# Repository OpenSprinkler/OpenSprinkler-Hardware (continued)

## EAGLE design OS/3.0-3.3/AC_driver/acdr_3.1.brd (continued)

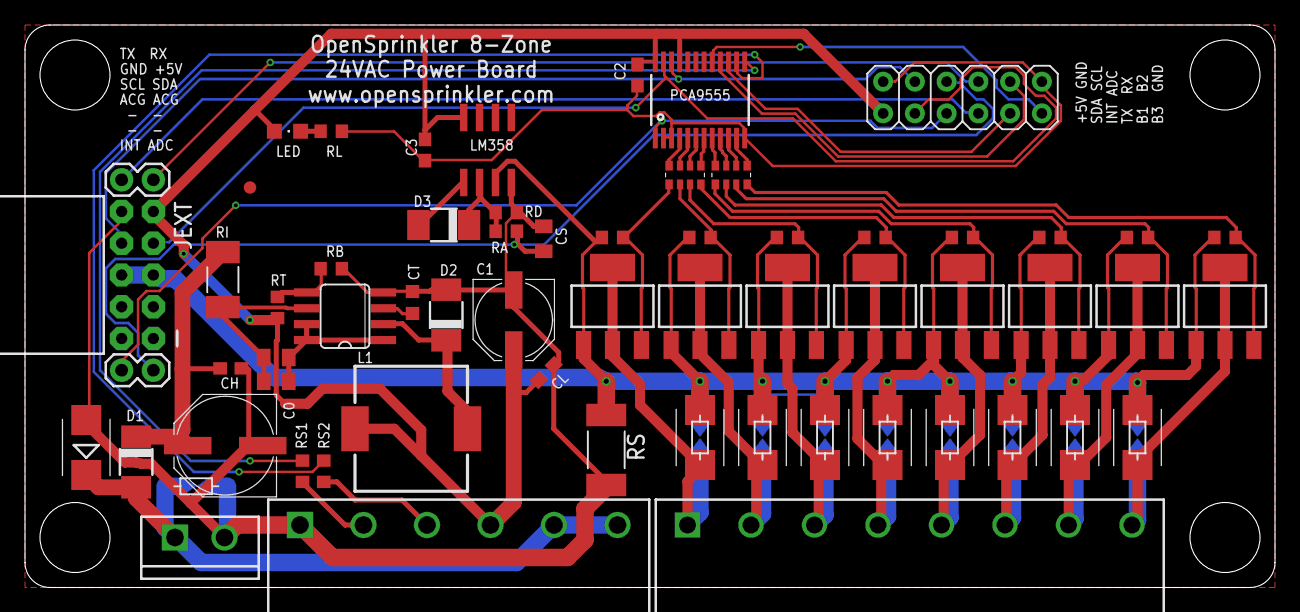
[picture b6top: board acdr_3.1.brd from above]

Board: 2 copper layers, 100.0 x 45.0 mm, 71 parts (0 on the bottom side), 50 nets.

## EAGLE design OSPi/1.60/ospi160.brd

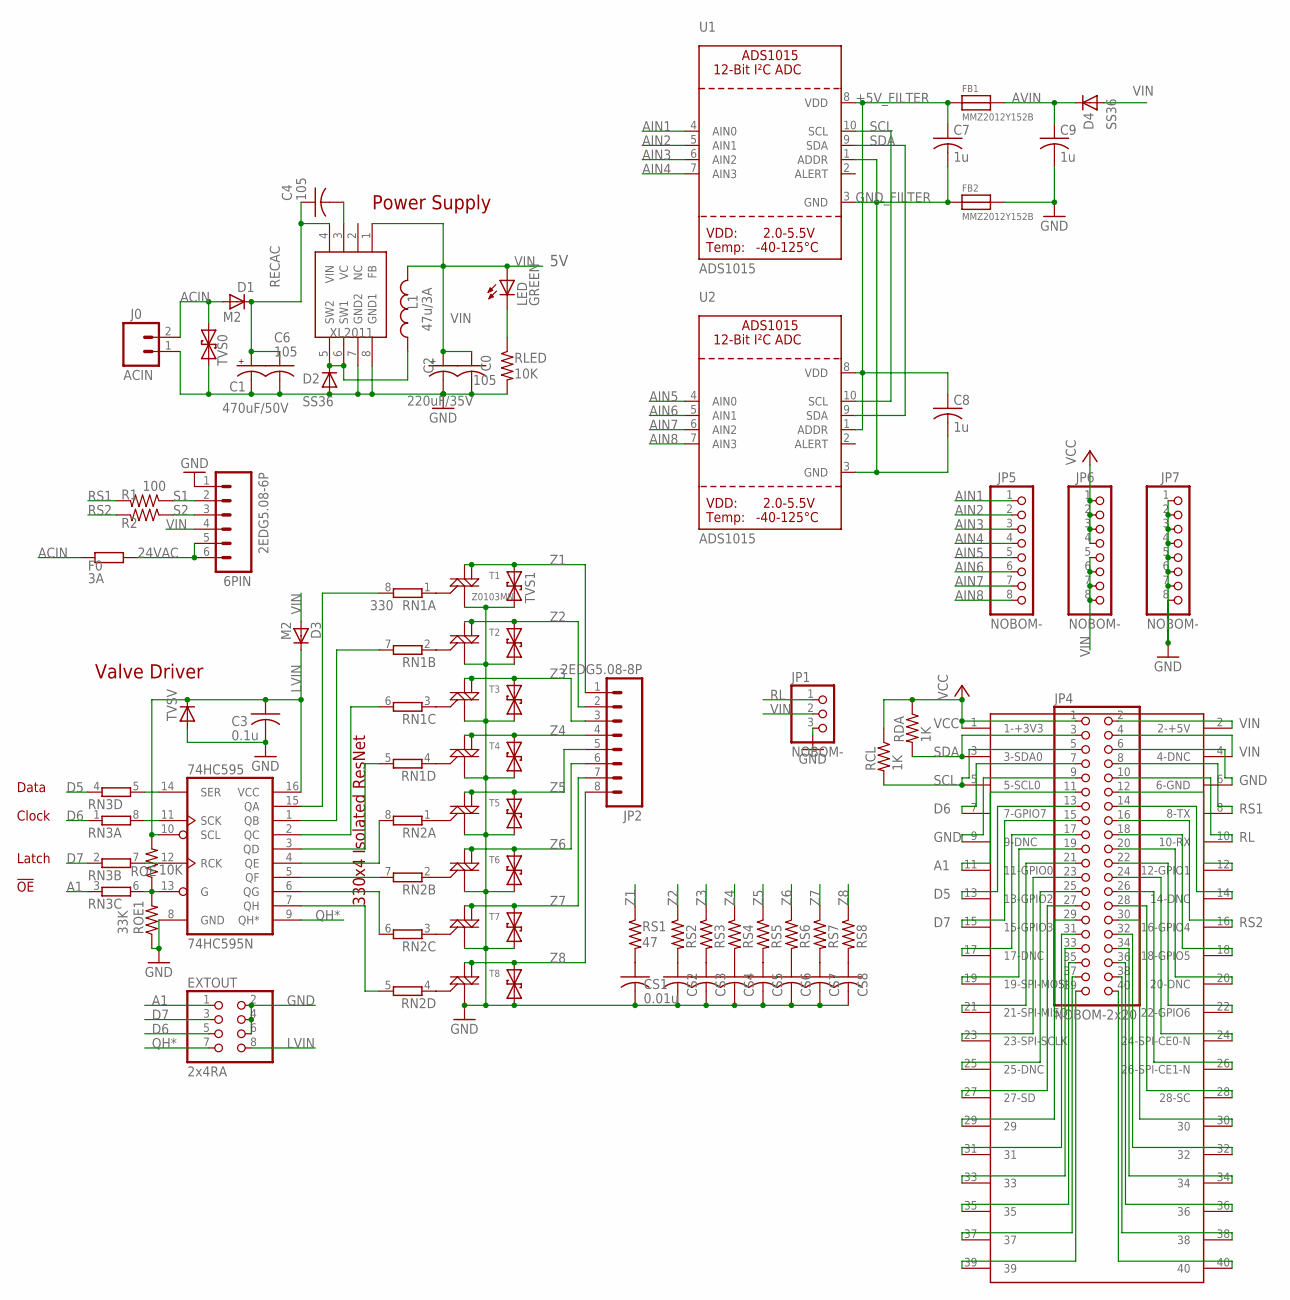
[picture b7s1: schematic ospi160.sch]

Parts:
6PIN: 2EDG5.08-6P; SCREWTERMINAL-5MM-6
74HC595: 74HC595N; SO16
C0, C4, C6: 105; C0603K
C1: 470uF/50V; E5-10,5
C2: 220uF/35V; E3,5-8
C3: 0.1u; C0603K
C7, C8, C9: 1u; C0603K
CS1, CS2, CS3, CS4, CS5, CS6, CS7, CS8: 0.01u; C0603K
D1, D3: M2; DO-214AC
D2, D4: SS36; SMB
EXTOUT: 2x4RA; 2X04/90
F0: 3A; 0207/15
FB1, FB2: MMZ2012Y152B; 0805
J0: ACIN; SCREWTERMINAL-4MM-2-X
JP1: NOBOM-; 1X03
JP2: 2EDG5.08-8P; SCREWTERMINAL-5MM-8
JP4: NOBOM-2x20; 2X20
JP5, JP6, JP7: NOBOM-; 1X08-CLEANBIG
L1: 47u/3A; YT1014
LED: GREEN; CHIPLED_0805
R1, R2: 100; R0603
RCL: 1K; R0603
RDA: 1K; R0603
RLED: 10K; R0603
RN1, RN2, RN3: 330; EXB38V
ROE: 10K; R0603
ROE1: 33K; R0603
RPI: RPIB+B+; RPIB+
RS1, RS2, RS3, RS4, RS5, RS6, RS7, RS8: 47; R0603
T1, T2, T3, T4, T5, T6, T7, T8: Z0103MN; SOT223
TVS0: TVSSMB; SMB
TVS1, TVS2, TVS3, TVS4, TVS5, TVS6, TVS7, TVS8: SMBJ43CA; SMB
TVSV: SMBJ5.0A; SMA-DIODE_ALT
U1, U2: ADS1015; MSOP10
XL2011: XL2011; SO08

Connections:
24VAC: 6PIN.5, 6PIN.6, F0.2
+5V_FILTER: C7.1, C8.1, FB1.1, U1.8 (VDD), U2.1 (ADDR), U2.8 (VDD)
A1: EXTOUT.1, JP4.11, RN3.3 (1), RPI.11 (11-GPIO0)
ACIN: D1.A, F0.1, J0.2, TVS0.C
AIN1: JP5.1, U1.4 (AIN0)
AIN2: JP5.2, U1.5 (AIN1)
AIN3: JP5.3, U1.6 (AIN2)
AIN4: JP5.4, U1.7 (AIN3)
AIN5: JP5.5, U2.4 (AIN0)
AIN6: JP5.6, U2.5 (AIN1)
AIN7: JP5.7, U2.6 (AIN2)
AIN8: JP5.8, U2.7 (AIN3)
AVIN: C9.1, D4.C, FB1.2
D5: JP4.13, RN3.4 (1), RPI.13 (13-GPIO2)
D6: EXTOUT.5, JP4.7, RN3.1, RPI.7 (7-GPIO7)
D7: EXTOUT.3, JP4.15, RN3.2 (1), RPI.15 (15-GPIO3)
GND: 6PIN.1, 74HC595.8 (GND), C0.2, C1.-, C2.-, C3.2, C6.2, C9.2, CS1.2, CS2.2, CS3.2, CS4.2, CS5.2, CS6.2, CS7.2, CS8.2, D2.A, EXTOUT.2, EXTOUT.4, EXTOUT.6, FB2.2, J0.1, JP1.3, JP4.6, JP4.9, JP7.1, JP7.2, JP7.3, JP7.4, JP7.5, JP7.6, JP7.7, JP7.8, RLED.2, ROE1.1, RPI.6 (6-GND), RPI.9 (9-DNC), T1.1 (M1), T2.1 (M1), T3.1 (M1), T4.1 (M1), T5.1 (M1), T6.1 (M1), T7.1 (M1), T8.1 (M1), TVS0.A, TVS1.C, TVS2.C, TVS3.C, TVS4.C, TVS5.C, TVS6.C, TVS7.C, TVS8.C, TVSV.A, XL2011.7 (GND2), XL2011.8 (GND1)
GND_FILTER: C7.2, C8.2, FB2.1, U1.1 (ADDR), U1.3 (GND), U2.3 (GND)
LVIN: 74HC595.10 (SCL), 74HC595.16 (VCC), C3.1, D3.C, EXTOUT.8, ROE.2, TVSV.C
unnamed: LED.C, RLED.1
unnamed: RN1.1, T1.3 (G)
unnamed: 74HC595.5 (QF), RN2.7 (2)
unnamed: 74HC595.6 (QG), RN2.6 (2)
unnamed: RN1.2 (1), T2.3 (G)
unnamed: 74HC595.7 (QH), RN2.5 (2)
unnamed: CS1.1, RS1.2
unnamed: CS2.1, RS2.2
unnamed: 74HC595.4 (QE), RN2.8 (2)
unnamed: 74HC595.3 (QD), RN1.5 (2)
unnamed: 74HC595.2 (QC), RN1.6 (2)
unnamed: 74HC595.1 (QB), RN1.7 (2)
unnamed: 74HC595.15 (QA), RN1.8 (2)
unnamed: RN1.3 (1), T3.3 (G)
unnamed: CS3.1, RS3.2
unnamed: CS4.1, RS4.2
unnamed: CS5.1, RS5.2
unnamed: RN1.4 (1), T4.3 (G)
unnamed: CS6.1, RS6.2
unnamed: RN2.1, T5.3 (G)
unnamed: CS7.1, RS7.2
unnamed: CS8.1, RS8.2
unnamed: D2.C, L1.P$1 (1), XL2011.5 (SW2), XL2011.6 (SW1)
unnamed: C4.2, XL2011.3 (VC)
unnamed: RN2.2 (1), T6.3 (G)
unnamed: RN2.3 (1), T7.3 (G)
unnamed: RN2.4 (1), T8.3 (G)
unnamed: 74HC595.14 (SER), RN3.5 (2)
unnamed: 74HC595.11 (SCK), RN3.8 (2)
unnamed: 74HC595.12 (RCK), RN3.7 (2)
unnamed: JP4.12, RPI.12 (12-GPIO1)
unnamed: JP4.14, RPI.14 (14-DNC)
unnamed: 74HC595.13 (G), RN3.6 (2), ROE.1, ROE1.2
unnamed: JP4.23, RPI.23 (23-SPI-SCLK)
unnamed: JP4.25, RPI.25 (25-DNC)
unnamed: JP4.27, RPI.27 (27-SD)
unnamed: JP4.29, RPI.29
unnamed: JP4.39, RPI.39
unnamed: JP4.37, RPI.37
unnamed: JP4.17, RPI.17 (17-DNC)
unnamed: JP4.19, RPI.19 (19-SPI-MOSI)
unnamed: JP4.21, RPI.21 (21-SPI-MISO)
unnamed: JP4.35, RPI.35
unnamed: JP4.33, RPI.33
unnamed: JP4.31, RPI.31
unnamed: JP4.34, RPI.34
unnamed: JP4.36, RPI.36
unnamed: JP4.38, RPI.38
unnamed: JP4.40, RPI.40
unnamed: JP4.18, RPI.18 (18-GPIO5)
unnamed: JP4.20, RPI.20 (20-DNC)
unnamed: JP4.22, RPI.22 (22-GPIO6)
unnamed: JP4.24, RPI.24 (24-SPI-CE0-N)
unnamed: JP4.26, RPI.26 (26-SPI-CE1-N)
unnamed: JP4.28, RPI.28 (28-SC)
unnamed: JP4.30, RPI.30
unnamed: JP4.32, RPI.32
QH*: 74HC595.9 (QH*), EXTOUT.7
RECAC: C1.+, C4.1, C6.1, D1.C, XL2011.4 (VIN)
RL: JP1.1, JP4.10, RPI.10 (10-RX)
RS1: JP4.8, R1.2, RPI.8 (8-TX)
RS2: JP4.16, R2.2, RPI.16 (16-GPIO4)
S1: 6PIN.2, R1.1
S2: 6PIN.3, R2.1
SCL: JP4.5, RCL.2, RPI.5 (5-SCL0), U1.10 (SCL), U2.10 (SCL)
SDA: JP4.3, RDA.2, RPI.3 (3-SDA0), U1.9 (SDA), U2.9 (SDA)
VCC: JP4.1, JP6.1, JP6.2, JP6.3, JP6.4, RCL.1, RDA.1, RPI.1 (1-+3V3)
VIN: 6PIN.4, C0.1, C2.+, D3.A, D4.A, JP1.2, JP4.2, JP4.4, JP6.5, JP6.6, JP6.7, JP6.8, L1.P$2 (2), LED.A, RPI.2 (2-+5V), RPI.4 (4-DNC), XL2011.1 (FB)
Z1: JP2.1, RS1.1, T1.2 (M2), T1.4 (M2-4), TVS1.A
Z2: JP2.2, RS2.1, T2.2 (M2), T2.4 (M2-4), TVS2.A
Z3: JP2.3, RS3.1, T3.2 (M2), T3.4 (M2-4), TVS3.A
Z4: JP2.4, RS4.1, T4.2 (M2), T4.4 (M2-4), TVS4.A
Z5: JP2.5, RS5.1, T5.2 (M2), T5.4 (M2-4), TVS5.A
Z6: JP2.6, RS6.1, T6.2 (M2), T6.4 (M2-4), TVS6.A
Z7: JP2.7, RS7.1, T7.2 (M2), T7.4 (M2-4), TVS7.A
Z8: JP2.8, RS8.1, T8.2 (M2), T8.4 (M2-4), TVS8.A

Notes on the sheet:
Power Supply
Valve Driver
Data
Clock
Latch
330x4 Isolated ResNet
!OE

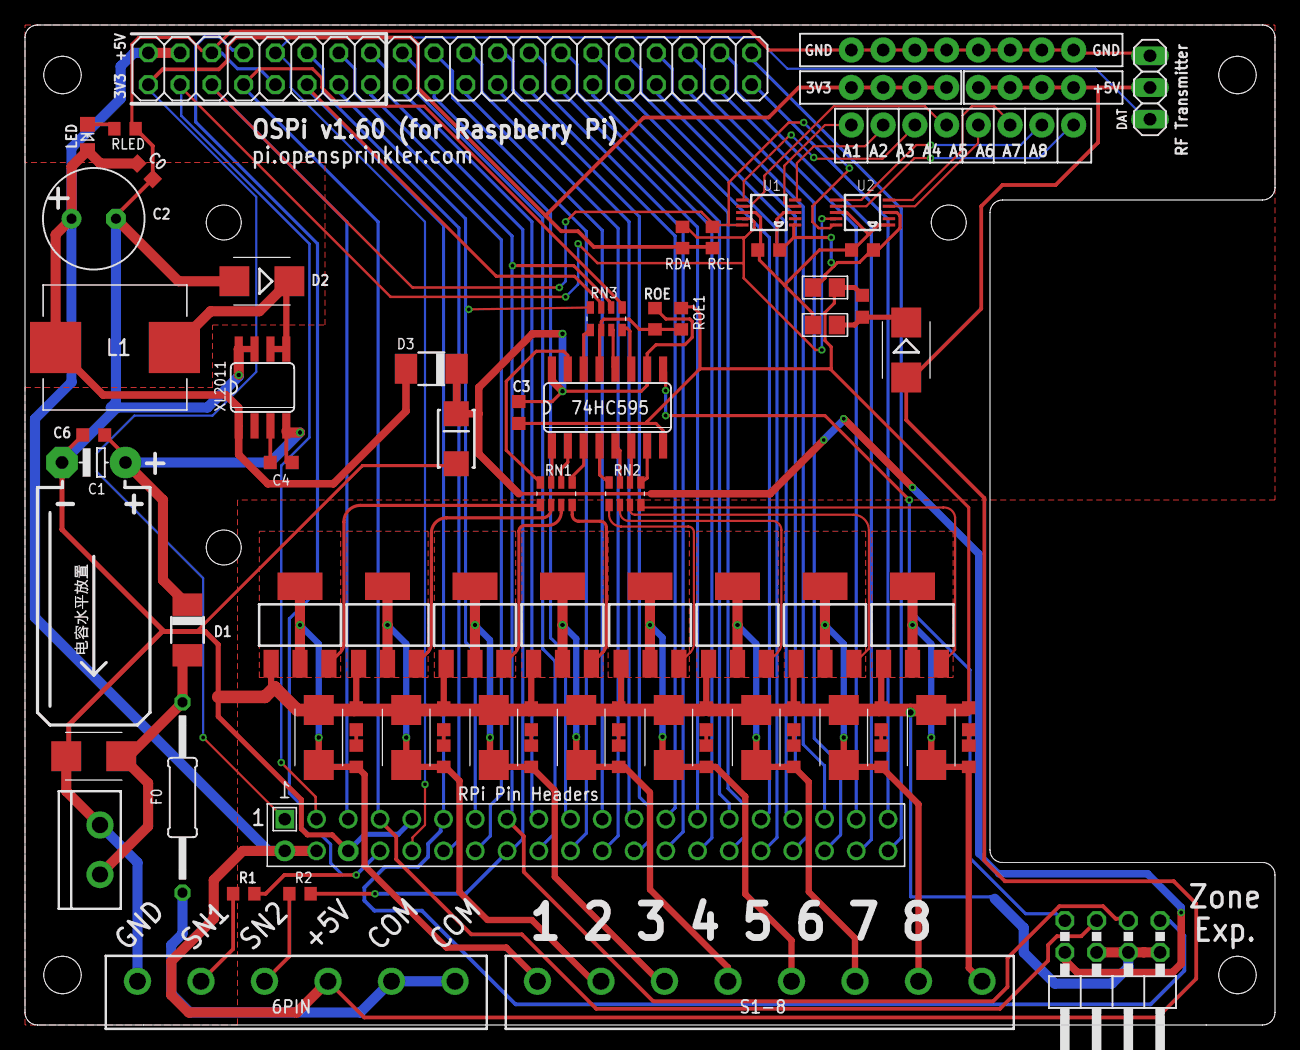
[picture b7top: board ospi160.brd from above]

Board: 2 copper layers, 100.0 x 80.0 mm, 76 parts (1 on the bottom side), 95 nets.

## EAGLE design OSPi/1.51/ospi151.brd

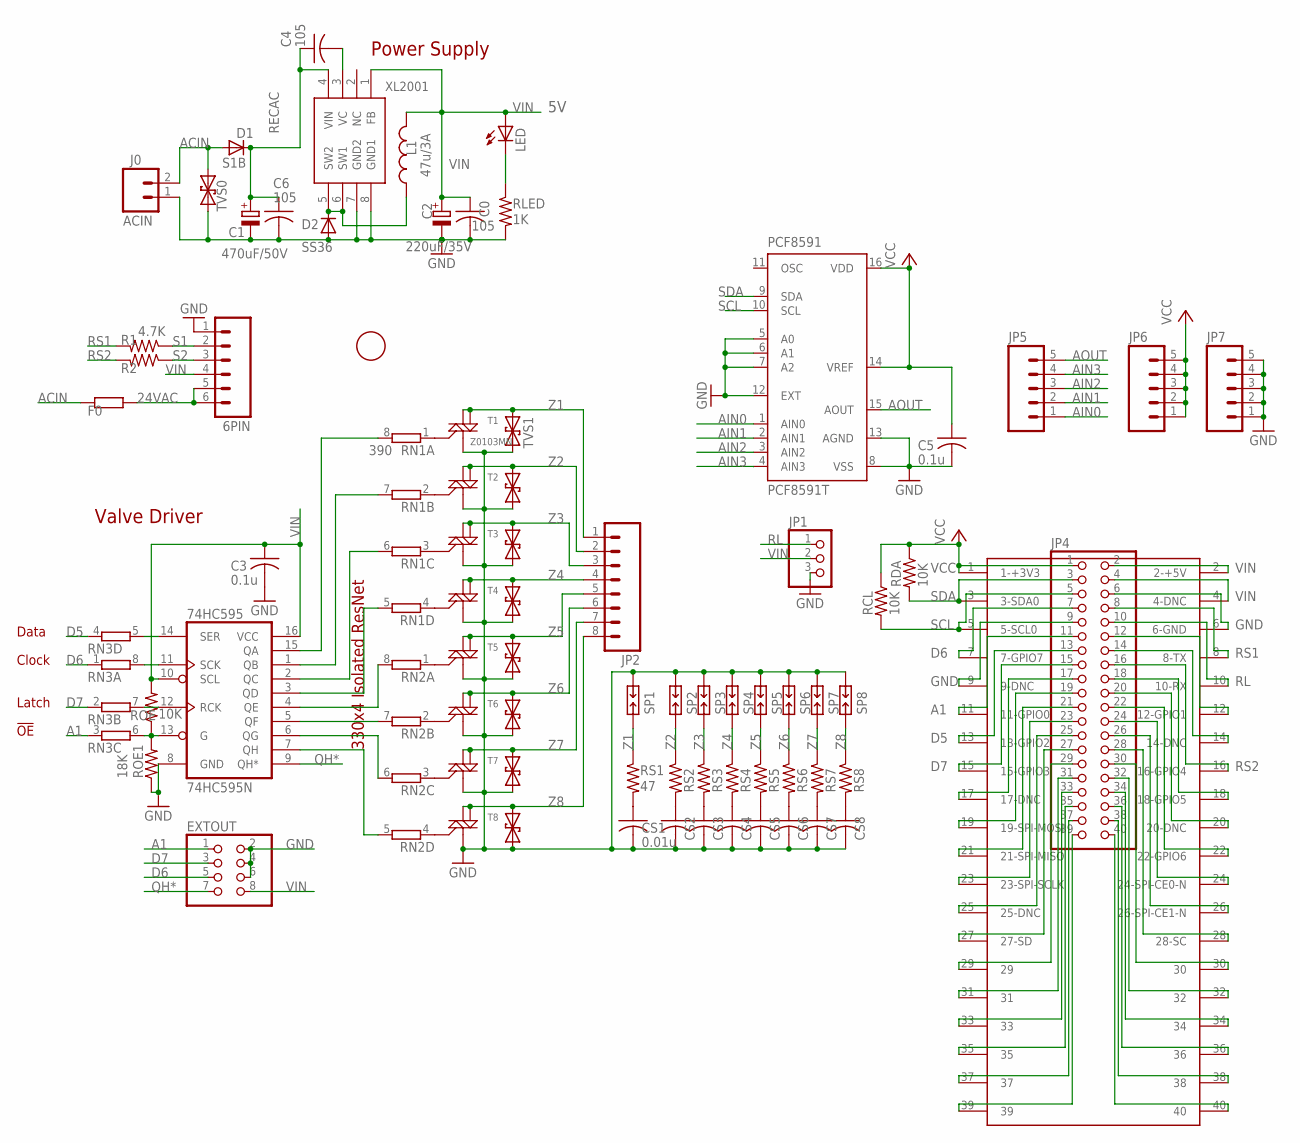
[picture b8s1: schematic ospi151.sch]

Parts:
1F: FIDUCIAL; FIDUCIAL_1MM
6PIN: M065MM; SCREWTERMINAL-5MM-6
74HC595: 74HC595N; SO16
C0, C4, C6: 105; C0603K
C1: 470uF/50V; E5-10,5
C2: 220uF/35V; E3,5-8
C3, C5: 0.1u; C0603K
CS1, CS2, CS3, CS4, CS5, CS6, CS7, CS8: 0.01u; C0603K
D1: S1B; DO-214AC
D2: SS36; SMB
EXTOUT: PINHD-2X4/90; 2X04/90
F0: R-EU_0207/15; 0207/15
J0: ACIN; SCREWTERMINAL-4MM-2-X
JP1: PINHD-1X3; 1X03
JP2: M085MM-8; SCREWTERMINAL-5MM-8
JP4: PINHD-2X20; 2X20
JP5, JP6, JP7: M05PTH; 1X05
L1: 47u/3A; YT1014
LED: LEDCHIPLED_0805; CHIPLED_0805
PCF8591: PCF8591T; SO16W
R1, R2: 4.7K; R0603
RCL: 10K; R0603
RDA: 10K; R0603
RLED: 1K; R0603
RN1, RN2, RN3: 390; EXB38V
ROE: 10K; R0603
ROE1: 18K; R0603
RS1, RS2, RS3, RS4, RS5, RS6, RS7, RS8: 47; R0603
SP1, SP2, SP3, SP4, SP5, SP6, SP7, SP8: PCB-SGAP
T1: Z0103MN; SOT223
T2, T3, T4, T5, T6, T7, T8: BT1308W; SOT223
TVS0, TVS1, TVS2, TVS3, TVS4, TVS5, TVS6, TVS7, TVS8: SMBJ45CA; SMB
U$2: RPIB+B+; RPIB+
XL2001: XL2011; SO08

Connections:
24VAC: 6PIN.5, 6PIN.6, F0.2
A1: EXTOUT.1, JP4.11, RN3.3 (1), U$2.11 (11-GPIO0)
ACIN: D1.A, F0.1, J0.2, TVS0.C
AIN0: JP5.1, PCF8591.1 (AIN0)
AIN1: JP5.2, PCF8591.2 (AIN1)
AIN2: JP5.3, PCF8591.3 (AIN2)
AIN3: JP5.4, PCF8591.4 (AIN3)
AOUT: JP5.5, PCF8591.15 (AOUT)
D5: JP4.13, RN3.4 (1), U$2.13 (13-GPIO2)
D6: EXTOUT.5, JP4.7, RN3.1, U$2.7 (7-GPIO7)
D7: EXTOUT.3, JP4.15, RN3.2 (1), U$2.15 (15-GPIO3)
GND: 6PIN.1, 74HC595.8 (GND), C0.2, C1.-, C2.-, C3.2, C5.2, C6.2, CS1.2, CS2.2, CS3.2, CS4.2, CS5.2, CS6.2, CS7.2, CS8.2, D2.A, EXTOUT.2, EXTOUT.4, EXTOUT.6, J0.1, JP1.3, JP4.6, JP4.9, JP7.1, JP7.2, JP7.3, JP7.4, JP7.5, PCF8591.5 (A0), PCF8591.6 (A1), PCF8591.7 (A2), PCF8591.8 (VSS), PCF8591.12 (EXT), PCF8591.13 (AGND), RLED.2, ROE1.1, SP1.1, SP2.1, SP3.1, SP4.1, SP5.1, SP6.1, SP7.1, SP8.1, T1.1 (M1), T2.1 (M1), T3.1 (M1), T4.1 (M1), T5.1 (M1), T6.1 (M1), T7.1 (M1), T8.1 (M1), TVS0.A, TVS1.C, TVS2.C, TVS3.C, TVS4.C, TVS5.C, TVS6.C, TVS7.C, TVS8.C, U$2.6 (6-GND), U$2.9 (9-DNC), XL2001.7 (GND2), XL2001.8 (GND1)
unnamed: LED.C, RLED.1
unnamed: RN1.1, T1.3 (G)
unnamed: 74HC595.5 (QF), RN2.7 (2)
unnamed: 74HC595.6 (QG), RN2.6 (2)
unnamed: RN1.2 (1), T2.3 (G)
unnamed: 74HC595.7 (QH), RN2.5 (2)
unnamed: CS1.1, RS1.2
unnamed: CS2.1, RS2.2
unnamed: 74HC595.4 (QE), RN2.8 (2)
unnamed: 74HC595.3 (QD), RN1.5 (2)
unnamed: 74HC595.2 (QC), RN1.6 (2)
unnamed: 74HC595.1 (QB), RN1.7 (2)
unnamed: 74HC595.15 (QA), RN1.8 (2)
unnamed: RN1.3 (1), T3.3 (G)
unnamed: CS3.1, RS3.2
unnamed: CS4.1, RS4.2
unnamed: CS5.1, RS5.2
unnamed: RN1.4 (1), T4.3 (G)
unnamed: CS6.1, RS6.2
unnamed: RN2.1, T5.3 (G)
unnamed: CS7.1, RS7.2
unnamed: CS8.1, RS8.2
unnamed: D2.C, L1.P$1 (1), XL2001.5 (SW2), XL2001.6 (SW1)
unnamed: C4.2, XL2001.3 (VC)
unnamed: RN2.2 (1), T6.3 (G)
unnamed: RN2.3 (1), T7.3 (G)
unnamed: RN2.4 (1), T8.3 (G)
unnamed: 74HC595.14 (SER), RN3.5 (2)
unnamed: 74HC595.11 (SCK), RN3.8 (2)
unnamed: 74HC595.12 (RCK), RN3.7 (2)
unnamed: JP4.12, U$2.12 (12-GPIO1)
unnamed: JP4.14, U$2.14 (14-DNC)
unnamed: 74HC595.13 (G), RN3.6 (2), ROE.1, ROE1.2
unnamed: JP4.23, U$2.23 (23-SPI-SCLK)
unnamed: JP4.25, U$2.25 (25-DNC)
unnamed: JP4.27, U$2.27 (27-SD)
unnamed: JP4.29, U$2.29
unnamed: JP4.39, U$2.39
unnamed: JP4.37, U$2.37
unnamed: JP4.17, U$2.17 (17-DNC)
unnamed: JP4.19, U$2.19 (19-SPI-MOSI)
unnamed: JP4.21, U$2.21 (21-SPI-MISO)
unnamed: JP4.35, U$2.35
unnamed: JP4.33, U$2.33
unnamed: JP4.31, U$2.31
unnamed: JP4.34, U$2.34
unnamed: JP4.36, U$2.36
unnamed: JP4.38, U$2.38
unnamed: JP4.40, U$2.40
unnamed: JP4.18, U$2.18 (18-GPIO5)
unnamed: JP4.20, U$2.20 (20-DNC)
unnamed: JP4.22, U$2.22 (22-GPIO6)
unnamed: JP4.24, U$2.24 (24-SPI-CE0-N)
unnamed: JP4.26, U$2.26 (26-SPI-CE1-N)
unnamed: JP4.28, U$2.28 (28-SC)
unnamed: JP4.30, U$2.30
unnamed: JP4.32, U$2.32
QH*: 74HC595.9 (QH*), EXTOUT.7
RECAC: C1.+, C4.1, C6.1, D1.C, XL2001.4 (VIN)
RL: JP1.1, JP4.10, U$2.10 (10-RX)
RS1: JP4.8, R1.2, U$2.8 (8-TX)
RS2: JP4.16, R2.2, U$2.16 (16-GPIO4)
S1: 6PIN.2, R1.1
S2: 6PIN.3, R2.1
SCL: JP4.5, PCF8591.10 (SCL), RCL.2, U$2.5 (5-SCL0)
SDA: JP4.3, PCF8591.9 (SDA), RDA.2, U$2.3 (3-SDA0)
VCC: C5.1, JP4.1, JP6.1, JP6.2, JP6.3, JP6.4, JP6.5, PCF8591.14 (VREF), PCF8591.16 (VDD), RCL.1, RDA.1, U$2.1 (1-+3V3)
VIN: 6PIN.4, 74HC595.10 (SCL), 74HC595.16 (VCC), C0.1, C2.+, C3.1, EXTOUT.8, JP1.2, JP4.2, JP4.4, L1.P$2 (2), LED.A, ROE.2, U$2.2 (2-+5V), U$2.4 (4-DNC), XL2001.1 (FB)
Z1: JP2.1, RS1.1, SP1.2, T1.2 (M2), T1.4 (M2-4), TVS1.A
Z2: JP2.2, RS2.1, SP2.2, T2.2 (M2), T2.4 (M2-4), TVS2.A
Z3: JP2.3, RS3.1, SP3.2, T3.2 (M2), T3.4 (M2-4), TVS3.A
Z4: JP2.4, RS4.1, SP4.2, T4.2 (M2), T4.4 (M2-4), TVS4.A
Z5: JP2.5, RS5.1, SP5.2, T5.2 (M2), T5.4 (M2-4), TVS5.A
Z6: JP2.6, RS6.1, SP6.2, T6.2 (M2), T6.4 (M2-4), TVS6.A
Z7: JP2.7, RS7.1, SP7.2, T7.2 (M2), T7.4 (M2-4), TVS7.A
Z8: JP2.8, RS8.1, SP8.2, T8.2 (M2), T8.4 (M2-4), TVS8.A

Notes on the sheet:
Power Supply
Valve Driver
Data
Clock
Latch
330x4 Isolated ResNet
!OE

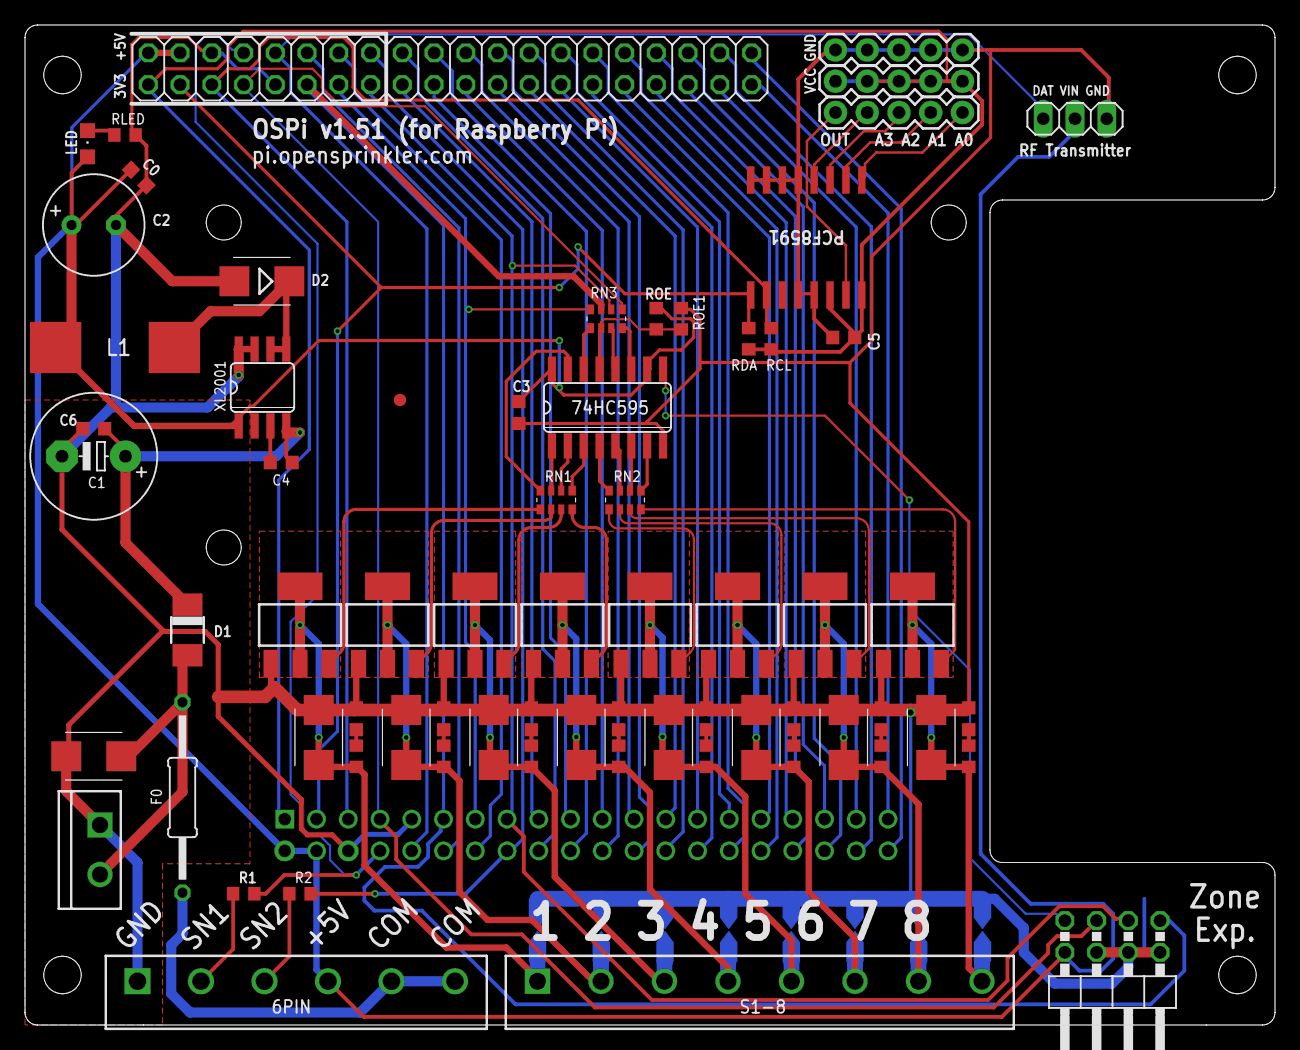
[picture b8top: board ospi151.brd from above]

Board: 2 copper layers, 100.0 x 80.0 mm, 77 parts (1 on the bottom side), 88 nets.

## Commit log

2017-06-06 add gitignore
2017-06-06 add all hardware design files
2018-06-08 add expander 3.0 revision 1
2018-06-08 change wording
2018-06-08 add OS3.0 revision 1 design; rename ac/dc driver board files
2018-06-08 add AC driver 3.1 and DC driver 3.1
2019-06-13 check in OS 3.2 design files; modify readme
2019-06-14 add latch 3.1 driver board
2020-06-19 add ospi 1.44, 1.5 hardware files; move ospi 1.43 files out of AC folder
2021-06-15 Added CC BY-SA 3.0 license because support said
    For hardware, we use Creative Commons CC BY-SA 3.0 license.
2021-06-15 Rename LICENSE to LICENSE.txt
2021-08-04 add OSPi 1.51 hardware design files
2021-09-10 add schematic PNG for acdr_3.2
2021-09-10 correct the pull down resistor value
2021-10-09 correcting os3.2 dc driver part number
2022-09-04 add ospi version 1.52 eagle files
2022-09-12 add ospi152 3D printable enclosure design
2022-09-13 check in laser cut acrylic enclosure design
2022-09-13 check in readme for laser cut design
2023-12-19 add OS3.3 master board design files
2024-04-23 add updated ac driver design files
2024-09-07 add OSPi v1.60 hardware design files
2024-09-26 add ospi20 hardware design files; reorganize enclosure folder
2024-09-27 check in ospi20 3D enclosure design
2025-05-08 add missing latch 3.2 files
2025-09-07 update license, readme, and reorganize folders
2025-09-07 update license
2025-09-22 add enclosure files for os3.3
2025-10-22 add dc 3.3 hardware files
2025-11-04 add image exports for os2.3 hardware design files
2026-04-25 add OS3.4 AC and DC files
2026-04-25 update READMEs
